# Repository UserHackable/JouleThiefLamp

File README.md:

## Steam Punk Joule Thief Flashlight Project

This is another one of my Cache Makers 4H projects. 

We used a ferrite core to wind a small transformer, an LED, a 2N3904 Transistor and a resistor to make a tiny boost circuit regulated only by the knee voltage of the LED. 

I designed the circuit board to be snapped in half, and sandwich the transformer. The whole thing was then put into a 1/2 inch copper pipe union, with a couple inches of copper pipe and a cap for a case. 

## JouleThiefLamp 

### Board dimensions

* (119996, 60000) original units
* (1.2000, 0.6000) inches
* (30.4790, 15.2400) mm

| Front | Back |
| --- | --- |
|  |  |

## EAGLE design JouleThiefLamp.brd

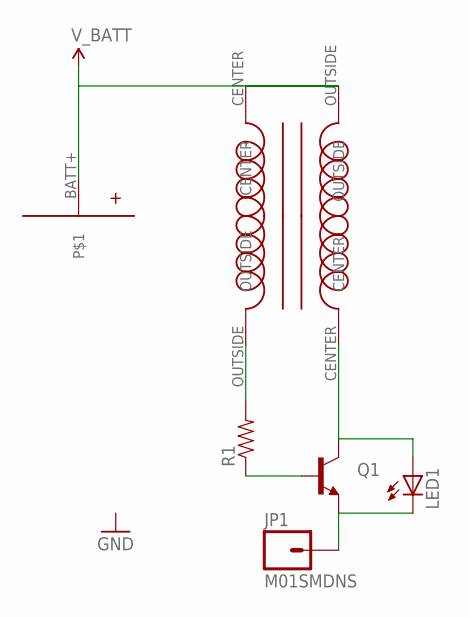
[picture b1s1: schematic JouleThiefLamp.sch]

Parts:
JP1: M01SMDNS; 1X01NS
LED1: LED5MM
Q1: TRANSISTOR_NPNTO-92-AMMO; TO-92-AMMO
R1: RESISTORPTH-1/4W-VERT; AXIAL-0.1
U$1: AA+BATT; AA+
U$2, U$3: HALF_CHOKE

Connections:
-: JP1.1, LED1.K (C), Q1.1 (E)
unnamed: R1.P$2 (2), U$3.OUTSIDE
unnamed: LED1.A, Q1.3 (C), U$3.CENTER
unnamed: Q1.2 (B), R1.P$1 (1)
V_BATT: U$1.BATT+, U$2.CENTER, U$2.OUTSIDE

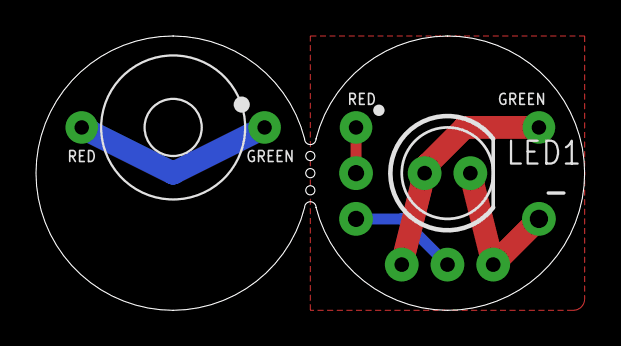
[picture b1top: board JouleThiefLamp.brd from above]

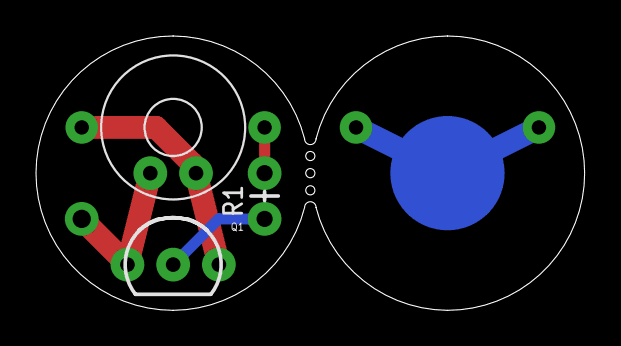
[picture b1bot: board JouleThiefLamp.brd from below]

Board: 2 copper layers, 30.5 x 15.2 mm, 7 parts (4 on the bottom side), 5 nets.

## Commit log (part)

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2016-04-08 from Makefile

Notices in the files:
parts and their libraries:
SparkFun-DiscreteSemi: Licensing: Creative Commons ShareAlike 4.0 International - https://creativecommons.org/licenses/by-sa/4.0
